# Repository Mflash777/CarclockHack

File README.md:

# HackClock GT: hypercar-shaped alarm clock, speaker, voice assistant + charging dock

A smart bedside clock shaped like an (original) hypercar, built for **Hack Club Half Life, week 4 (displays)**.
It can replace an Alexa and a pile of chargers:

- **Time on the windshield**: a 7-segment display behind smoked glass
- **Info screen in the left door**: 2.0" TFT
- **Watch charging on the roof**: Samsung's magnetic puck sits flush in a round pocket in the middle of the roof

- **7-segment display (HT16K33)**: big, bright time you can read from bed
- **2.0" TFT (ST7789)**: weather, **live stocks**, **news**, **phone messages**, and **Now playing**
- **Bluetooth speaker**: pair your phone with "HackClock" and play music through a 2" speaker (MAX98357A amp)
- **Voice assistant**: say the wake word (or press TALK) and ask for alarms, timers, weather, stocks,
  news, music control, or smart-home commands, through your own **Home Assistant** server
- **Alarms** through the speaker (gentle volume ramp), with two **buzzers** as a backup
- **Slap the spoiler** to stop the alarm (the wing is a big hinged button), plus **MODE** and **TALK** buttons in the left door beside the screen
- **DS3231 real-time clock**: keeps time and alarms going if WiFi drops
- **Web settings page** at `http://hackclock.local`
- **3D-printed hypercar body** (original design: low nose, flared fenders, splitter, hinged rear wing; 254 x 134 x 80 mm) + custom 2-layer carrier PCB

### Everything in place

**Top cover lifted off** (hood + roof + windshield, plus the wing and its switch; the body is really one print, this just shows the inside) - what is inside:

**Under the top cover**: the microphone, 7-segment display, the watch puck's pocket and the spoiler's switch stand:

## What's in this repo

| Folder | What |
|---|---|
| `firmware/clock/` | PlatformIO project for the **XIAO ESP32-S3** (displays, buttons, mic, voice, WiFi data) |
| `firmware/audio-board/` | PlatformIO project for the **ESP32 WROVER** (Bluetooth speaker, voice replies, tones) |
| `hardware/schematic/` | `schematic.pdf` (2 sheets: clock PCB, audio board + system) |
| `hardware/pcb/` | `hackclock.kicad_pcb` (KiCad 8, fully routed) + generator + preview |
| `case/` | `stl/` ready to print (body, wing, bottom plate, wheel x4, windshield, side glass x2); `case_gen.py` = parametric source |
| `docs/WIRING.md` | pin maps, every connection, soldering + mounting |
| `docs/HOME_ASSISTANT.md` | voice setup step by step + what you can say |
| `BOM.csv` | bill of materials (~$71; your Samsung chargers are reused) |

## How it works

```
   Phone ──Bluetooth──►  AUDIO BOARD (ESP32 WROVER) ──I2S──► MAX98357A ──► 2" speaker
                              ▲  │ dims TFT backlight
                     I2C 0x42 │  │ downloads spoken replies (MP3) over WiFi
                              ▼  ▼
   USB-C 5V ────────► CLOCK BOARD (XIAO ESP32-S3) ◄──WiFi──► Home Assistant (wake word, Whisper, Piper)
                │ SPI: TFT        │ I2C: 7-segment, RTC     │ I2S: INMP441 mic
                │ ADC: 3 switches │ PWM: backup buzzers     └──► internet: weather, stocks, news, ntfy
   your Samsung watch puck (middle of the roof): own cable, out through a USB-A slot in the tail
```

**Why two ESP32s?** Phones send music over *Bluetooth Classic*, which the ESP32-S3 doesn't have.
The original ESP32 does, so it acts as the speaker, and the S3 does everything else. They talk over
the same I2C bus as the RTC and 7-segment display.

**Voice:** the clock streams 16 kHz audio from the INMP441 mic to Home Assistant's
[Assist pipeline](https://developers.home-assistant.io/docs/voice/pipelines/) over a WebSocket.
HA detects the wake word and turns your speech into text. The clock handles clock-type commands
itself; anything else (lights, questions) goes to HA's conversation agent. HA turns the reply into
speech, and the audio board plays it while pausing your music.

The 3 switches (spoiler, MODE, TALK) share **one** analog pin through a resistor ladder, which is how everything fits on the XIAO.

## Bill of materials (short)  (buy links: docs/BOM_LINKS.md)

| Part | ~USD |
|---|---|
| Seeed XIAO ESP32-S3 + ESP32 WROVER dev board | 16.50 |
| 2.0" ST7789 TFT + HT16K33 7-segment + DS3231 RTC | 11.50 |
| INMP441 mic, MAX98357A amp, 2" 4 ohm speaker | 8.50 |
| 2 push buttons + spoiler switch, 2 buzzers, USB-C breakout, small parts, wires, screws, tape | ~9 |
| PCB + shipping | ~17 |
| PETG filament (body, wheels, smoke "glass") | 8.50 |
| **Total** | **~$71** |

Already yours: the Samsung watch puck and its adapter, plus a USB-C charger for the clock.
Not included: a Home Assistant server for voice. Full list: [`BOM.csv`](BOM.csv).

## Build it

1. **Order the PCB**: open `hardware/pcb/hackclock.kicad_pcb` in KiCad 8, press **B** (fills
   the ground planes), run **Inspect > Design Rules Checker**, then **File > Fabrication Outputs >
   Gerbers + Drill Files**. Zip and upload to JLCPCB.
2. **Print the car**: needs a **256 mm bed**. Body upright (open bottom down, tree supports),
   bottom plate flat, 4 wheels in black, windshield + 2 side glass in translucent smoke PETG.
   The wing prints on its own (upside down as exported, no supports needed beyond a brim). PETG, 0.2 mm, 3 walls, 15% infill. Measure your TFT and watch puck first; if they
   differ, change `TFT_POCKET` or `PUCK` at the top of `case/case_gen.py` and run it again.
3. **Solder + wire**: [`docs/WIRING.md`](docs/WIRING.md), including the spoiler button (section 3c).
4. **Flash both boards** (VS Code + PlatformIO extension):
   - open `firmware/audio-board`, plug in the ESP32 WROVER, click **Upload**
   - open `firmware/clock`, plug in the XIAO, click **Upload** (hold **B** while plugging in if it won't upload)

## First-time setup

1. Plug a USB-C charger into the tail. The door screen says *join HackClock-Setup*.
2. Join WiFi **HackClock-Setup** on your phone, choose your home WiFi and type the password.
3. Open **http://hackclock.local** and set alarms, stocks (free Finnhub key), location, time zone, volume.
4. **Bluetooth:** on your phone, pair with **HackClock** and play something.
5. **Voice:** follow [`docs/HOME_ASSISTANT.md`](docs/HOME_ASSISTANT.md), then paste your HA address + token on the web page.
6. **Charging:** snap the watch onto the puck in the middle of the roof, with its strap running **side to side**
   (so it drapes over the sides, not toward the windshield).

## Phone messages

Install the free **ntfy** app and subscribe to the topic shown on the home page (e.g.
`hackclock-3fa29c1b`). Anything you send shows on the clock with a chime, and you can say
"read my messages". From a laptop: `curl -d "Dinner is ready!" ntfy.sh/<your topic>`.

## Buttons

| Button | Normal | On "Now playing" | Alarm ringing | Setting an alarm |
|---|---|---|---|---|
| **Slap the spoiler** | night dim on/off | | **stop** the alarm | |
| **Spoiler** held 1.5 s | cancel pending snooze | play / pause | | |
| **MODE** | next page | next page | **snooze** 9 min | |
| **MODE** held 1.5 s | brightness +1 (wraps) | | | |
| **MODE** held 8 s | forget the WiFi (re-run setup) | | | |
| **TALK** | talk to the assistant | | stop | |
| **TALK** held | wake word on/off | | | |

There are no UP/DOWN buttons. Set alarms, volume, brightness and time zone on the settings page
(`http://hackclock.local`) or by voice. The time sets itself from the internet.

## Regenerating the design files

```bash
cd hardware/pcb && python3 generate_pcb.py && python3 render_pcb.py
cd hardware/schematic && python3 draw_schematic.py
cd case && python3 case_gen.py && python3 check_stl.py && python3 render_case.py   # car body
cd case && python3 render_assembly.py                                           # all parts in place + top cover off
```
Only `numpy` and `matplotlib` are needed.

## Status / known limits

- The firmware was written against Arduino-ESP32 2.0.x (PlatformIO `espressif32@6.9.0`) and **has not been
  compiled or run on hardware yet**. Expect a few small fixes on the first build.
- No echo cancellation: the wake word struggles over loud music, but TALK always works.
- WiFi and Bluetooth share one radio on the audio board, so music can stutter briefly while a voice reply downloads.
- Voice needs a Home Assistant server; the clock, speaker, stocks, news and messages all work without one.
- The speaker fires down at the desk, so it sounds best on a hard, flat surface.

---
Made for Hack Club Half Life. MIT licence.

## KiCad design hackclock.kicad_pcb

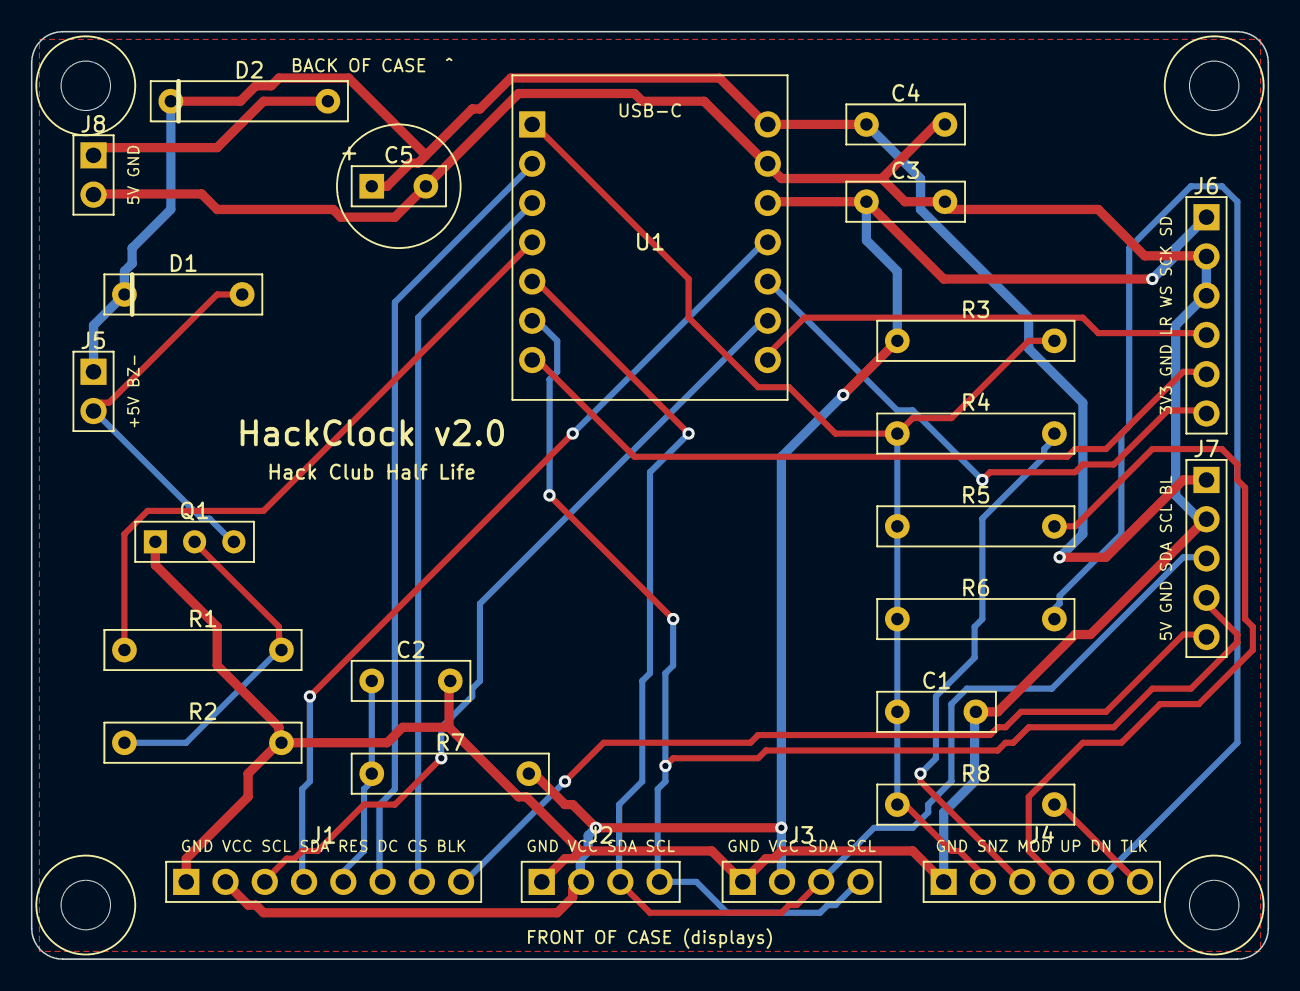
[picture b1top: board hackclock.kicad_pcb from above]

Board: 2 copper layers, 80.0 x 60.0 mm, 29 parts (0 on the bottom side), 23 nets.

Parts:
C1: 100nF; C_Disc_P5.08mm
C2: 1uF; C_Disc_P5.08mm
C3, C4: 10uF; C_Disc_P5.08mm
C5: 470uF; CP_Radial_D8.0mm_P3.50mm
D1: 1N4148; D_DO-35_P7.62mm
D2: 1N5819; D_DO-41_P10.16mm
H1, H2, H3, H4: M3; MountingHole_3.2mm_M3
J1: TFT; PinHeader_1x08_P2.54mm
J2: 7SEG_I2C; PinHeader_1x04_P2.54mm
J3: RTC; PinHeader_1x04_P2.54mm
J4: BUTTONS; PinHeader_1x06_P2.54mm
J5: BUZZERS; PinHeader_1x02_P2.54mm
J6: MIC; PinHeader_1x06_P2.54mm
J7: AUDIO; PinHeader_1x05_P2.54mm
J8: 5V_IN; PinHeader_1x02_P2.54mm
Q1: 2N3904; TO-92_Inline
R1: 1k; R_Axial_P10.16mm
R2, R3, R6, R7: 10k; R_Axial_P10.16mm
R4: 2k2; R_Axial_P10.16mm
R5: 4k7; R_Axial_P10.16mm
R8: 15k; R_Axial_P10.16mm
U1: XIAO_ESP32S3; Seeed_XIAO_Socket

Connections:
+3V3: C3.1, J1.2, J2.2, J3.2, J6.1, R3.1, R7.2, U1.10
+5V: C4.1, C5.1, D1.1, D2.1, J5.1, J7.1, U1.8
+5V_IN: D2.2, J8.1
BTN: C1.1, J4.2, R3.2, R4.1, R5.1, R6.1, R8.1, U1.1
BUZ: R1.1, U1.4
BZ_N: D1.2, J5.2, Q1.3
DOWN_N: J4.5, R6.2
GND: C1.2, C2.2, C3.2, C4.2, C5.2, J1.1, J2.1, J3.1, J4.1, J6.2, J6.3, J7.2, J8.2, Q1.1, R2.2, U1.9
MIC_SCK: J6.5, U1.7
MIC_SD: J6.6, U1.12
MIC_WS: J6.4, U1.14
MODE_N: J4.3, R4.2
Q_B: Q1.2, R1.2, R2.1
SCL: J2.4, J3.4, J7.4, U1.6
SDA: J2.3, J3.3, J7.3, U1.5
TALK_N: J4.6, R8.2
TFT_BL: J1.8, J7.5
TFT_CS: J1.7, U1.3
TFT_DC: J1.6, U1.2
TFT_MOSI: J1.4, U1.11
TFT_RST: C2.1, J1.5, R7.1
TFT_SCK: J1.3, U1.13
UP_N: J4.4, R5.2

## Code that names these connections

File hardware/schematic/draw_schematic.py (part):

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box(212, 250, 40, 26, "J3  DS3231 RTC", "I2C 0x68, CR2032 backup")
pins(252, 270, ["GND", "VCC", "SDA", "SCL"], ["GND", "+3V3", "SDA", "SCL"], "right")
box(306, 238, 40, 38, "J6  INMP441 microphone", "I2S, 16 kHz, L/R = GND")
pins(346, 270, ["VDD", "GND", "L/R", "WS", "SCK", "SD"], ["+3V3", "GND", "GND", "MIC_WS", "MIC_SCK", "MIC_SD"], "right")

box(150, 160, 52, 50, "U1  Seeed XIAO ESP32-S3", "")
pins(150, 204, ["D0/GPIO1", "D1/GPIO2", "D2/GPIO3", "D3/GPIO4", "D4/GPIO5", "D5/GPIO6", "D6/GPIO43"],
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     ["+5V", "GND", "+3V3", "TFT_MOSI", "MIC_SD", "TFT_SCK", "MIC_WS"], "right", pitch=7)

box(306, 178, 40, 32, "J7  AUDIO link", "to audio board (sheet 2)")
pins(346, 204, ["5V", "GND", "SDA", "SCL", "BL"], ["+5V", "GND", "SDA", "SCL", "TFT_BL"], "right")

# power in + bulk caps
ax.text(262, 158, "Power in + bulk capacitors", fontsize=8, fontweight="bold")
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# TFT reset
ax.text(22, 205, "TFT power-on reset", fontsize=8, fontweight="bold")
vcc(40, 192, "+3V3"); resistor_v(40, 192, 172, "R7", "10k")
line([(40, 172), (40, 166)]); dot(40, 172); line([(40, 172), (55, 172)]); label(55, 172, "TFT_RST", "right")
cap_v(40, 166, 152, "C2", "1uF"); gnd(40, 152)

# buzzer driver
ax.text(22, 132, "Backup buzzers (2 passive, parallel) via J5", fontsize=8, fontweight="bold")
line([(30, 92), (40, 92)]); label(30, 92, "BUZ", "left")
resistor_h(40, 62, 92, "R1", "1k"); line([(62, 92), (72, 92)]); dot(66, 92)
resistor_v(66, 92, 70, "R2", "10k"); gnd(66, 70)
ax.add_patch(Circle((80, 92), 8, fill=False, ec=INK, lw=1.3))
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ax.text(176, 140, "Buttons: resistor ladder on one ADC pin (J4)", fontsize=8, fontweight="bold")
vcc(186, 126, "+3V3"); resistor_v(186, 126, 108, "R3", "10k")
line([(186, 108), (186, 100)]); dot(186, 100)
line([(166, 100), (330, 100)]); label(166, 100, "BTN", "left")
cap_v(176, 100, 86, "C1", "100nF"); gnd(176, 86); dot(176, 100)
def button(x, y_top, y_bot, name):
    line([(x, y_top), (x, y_top - 3)])
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    if x != 316: dot(x, 100)
    resistor_v(x, 100, 84, r, val); button(x, 84, 58, nm)
ax.text(176, 46, "Released 3.3 V | SNOOZE (spoiler) 0 V | MODE 0.6 V | TALK 1.98 V   (UP / DOWN: leave the buttons off)", fontsize=6.8, color="#555")
ax.text(176, 40, "J4: GND, SNZ (spoiler switch), MODE_N, UP_N, DOWN_N (unused), TALK_N - each switch wires between its pin and GND", fontsize=6.3, color="#555")

notes = ["NOTES",
         "1. All modules run at 3.3 V; only the buzzers, amp and audio board use 5 V.",
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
